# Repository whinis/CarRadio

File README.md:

# CarRadio
An atempt at making a fully featured car radio

There will be folders for each modules of the radio as well as one for the final board and all code needed to run the radio minus the si4689 firmware files

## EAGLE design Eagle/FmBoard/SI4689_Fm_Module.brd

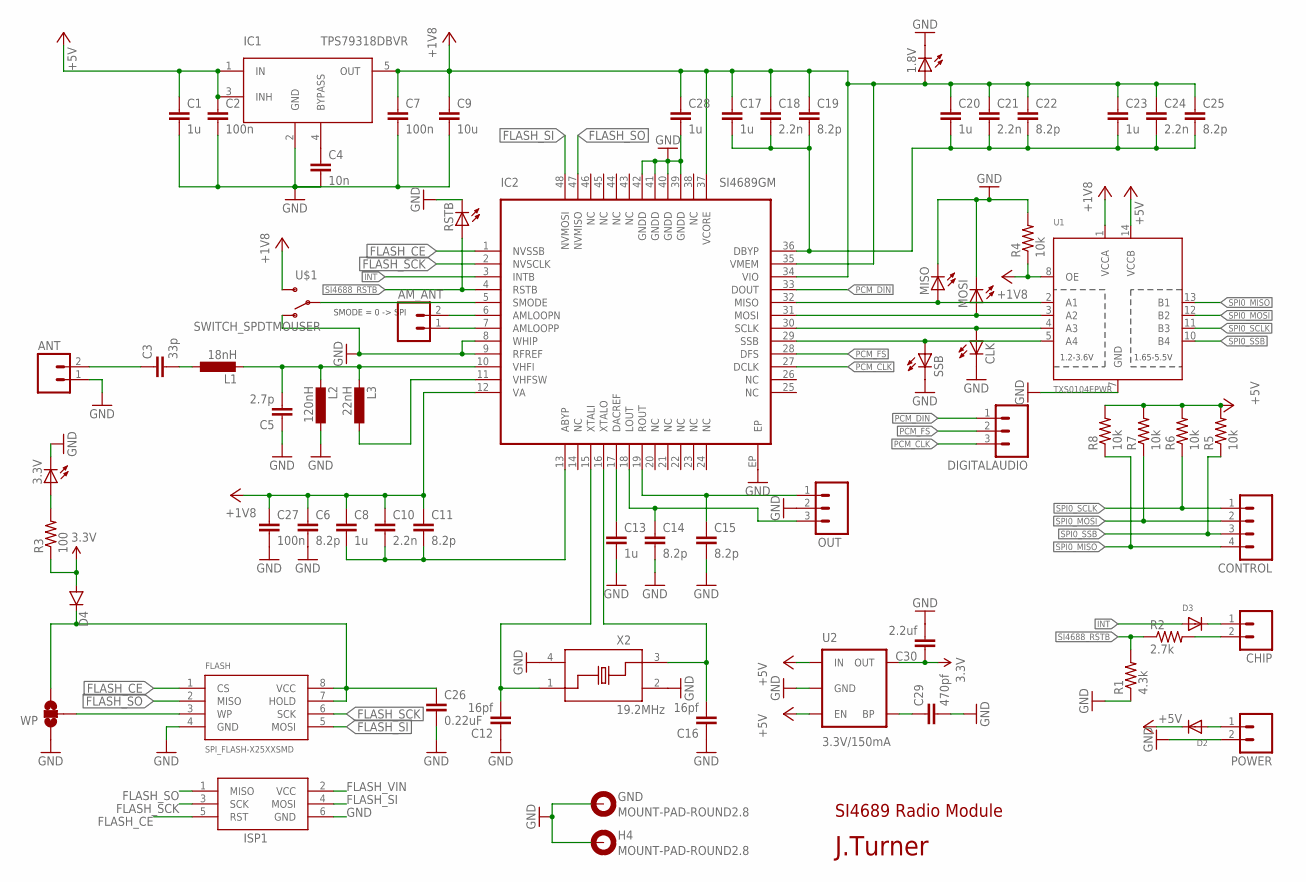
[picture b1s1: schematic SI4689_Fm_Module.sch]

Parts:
1.8V, 3.3V: LED_ESML0603; LED_SML0603
AM_ANT: M02; 02P
ANT: M02; 02P
C1, C8, C13, C17, C20, C23, C28: 1u; SMD0603
C2, C7, C27: 100n; SMD0603
C3: 33p; 0603-CAP
C4: 10n; SMD0603
C5: 2.7p; 0603-CAP
C6, C11, C14, C15, C19, C22, C25: 8.2p; SMD0603
C9: 10u; SMD0603
C10, C18, C21, C24: 2.2n; SMD0603
C12, C16: 16pf; 0603-CAP
C26: 0.22uF; 0603-CAP
C29: 470pf; 0603-CAP
C30: 2.2uf; 0603-CAP
CHIP: M02; 02P
CLK: LED_ESML0603; LED_SML0603
CONTROL: M04; 04P
D2, D3: DIODESOD-323F; SOD-323F
D4: DIODESOD523; SOD523
DIGITALAUDIO: M03; 03P
FLASH: SPI_FLASH-X25XXSMD; SO08
GND: MOUNT-PAD-ROUND2.8; 2,8-PAD
H4: MOUNT-PAD-ROUND2.8; 2,8-PAD
IC1: TPS79318DBVR; SOT23-5
IC2: SI4689GM; QFN48
ISP1: AVRISP-6; AVRISP
L1: 18nH; SMD0402
L2: 120nH; SMD0402
L3: 22nH; SMD0402
MISO: LED_ESML0603; LED_SML0603
MOSI: LED_ESML0603; LED_SML0603
OUT: M03; 03P
POWER: M02; 02P
R1: 4.3k; 0603-RES
R2: 2.7k; 0603-RES
R3: 100; 0603-RES
R4, R5, R6, R7, R8: 10k; 0603-RES
RSTB: LED_ESML0603; LED_SML0603
SSB: LED_ESML0603; LED_SML0603
U1: TXS0104EPWR; TSSOP14
U2: 3.3V/150mA; SOT23-5
U$1: SWITCH_SPDTMOUSER; SSSS810701
WP: SOLDERJUMPER_2WAYS; SJ_3
X2: 19.2MHz; XTAL_3.2X2.5

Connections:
3.3V: C30.1, D4.A, R3.1, U2.5 (OUT)
+1V8: 1.8V.A, C6.1, C7.1, C8.1, C9.1, C10.1, C11.1, C17.1, C18.1, C19.1, C20.1, C21.1, C22.1, C23.1, C24.1, C25.1, C27.1, C28.1, IC1.5 (OUT), IC2.12 (VA), IC2.34 (VIO), IC2.35 (VMEM), IC2.37 (VCORE), R4.1, U1.1 (VCCA), U1.8 (OE), U$1.S
FLASH_CE: FLASH.1 (CS), IC2.1 (NVSSB), ISP1.5 (RST)
FLASH_SCK: FLASH.6 (SCK), IC2.2 (NVSCLK), ISP1.3 (SCK)
FLASH_SI: FLASH.5 (MOSI), IC2.48 (NVMOSI), ISP1.4 (MOSI)
FLASH_SO: FLASH.2 (MISO), IC2.47 (NVMISO), ISP1.1 (MISO)
FLASH_VIN: C26.1, D4.C, FLASH.7 (HOLD), FLASH.8 (VCC), ISP1.2 (VCC), WP.3
GND: 1.8V.C, 3.3V.C, ANT.1, C1.2, C2.2, C4.2, C5.1, C6.2, C7.2, C9.2, C12.1, C13.2, C14.2, C15.2, C16.1, C26.2, C27.2, C28.2, C29.2, C30.2, CLK.C, FLASH.4 (GND), GND.B2,8, H4.B2,8, IC1.2 (GND), IC2.8 (WHIP), IC2.9 (RFREF), IC2.39 (GNDD), IC2.40 (GNDD), IC2.41 (GNDD), IC2.42 (GNDD), IC2.EP, ISP1.6 (GND), L2.1, MISO.C, MOSI.C, OUT.2, POWER.2, R1.1, R4.2, RSTB.C, SSB.C, U1.7 (GND), U2.2 (GND), U$1.O, WP.1, X2.2 (GND), X2.4 (GND)
INT: D3.A, IC2.3 (INTB)
LDO_IN: C1.1, C2.1, D2.C, IC1.1 (IN), IC1.3 (INH), R5.2, R6.2, R7.2, R8.2, U1.14 (VCCB), U2.1 (IN), U2.3 (EN)
unnamed: C3.2, L1.1
unnamed: C5.2, IC2.10 (VHFI), L1.2, L2.2, L3.2
unnamed: IC2.11 (VHFSW), L3.1
unnamed: C8.2, C10.2, C11.2, IC2.13 (ABYP)
unnamed: C17.2, C18.2, C19.2, C20.2, C21.2, C22.2, C23.2, C24.2, C25.2, IC2.36 (DBYP)
unnamed: C12.2, IC2.15 (XTALI), X2.1
unnamed: C16.2, IC2.16 (XTALO), X2.3
unnamed: C13.1, IC2.17 (DACREF)
unnamed: CHIP.1, D3.C
unnamed: C4.1, IC1.4 (BYPASS)
unnamed: C29.1, U2.4 (BP)
unnamed: 3.3V.A, R3.2
unnamed: FLASH.3 (WP), WP.2
unnamed: AM_ANT.1, IC2.7 (AMLOOPP)
unnamed: AM_ANT.2, IC2.6 (AMLOOPN)
unnamed: IC2.5 (SMODE), U$1.P
unnamed: CHIP.2, R2.2
unnamed: D2.A, POWER.1
PCM_CLK: DIGITALAUDIO.3, IC2.27 (DCLK)
PCM_DIN: DIGITALAUDIO.1, IC2.33 (DOUT)
PCM_FS: DIGITALAUDIO.2, IC2.28 (DFS)
RF_IN: ANT.2, C3.1
SI4688_LOUT: C14.1, IC2.18 (LOUT), OUT.3
SI4688_ROUT: C15.1, IC2.19 (ROUT), OUT.1
SI4688_RSTB: IC2.4 (RSTB), R1.2, R2.1, RSTB.A
SPI0_CE0_N18: IC2.29 (SSB), SSB.A, U1.5 (A4)
SPI0_MISO: CONTROL.4, R8.1, U1.13 (B1)
SPI0_MISO18: IC2.32 (MISO), MISO.A, U1.2 (A1)
SPI0_MOSI: CONTROL.2, R7.1, U1.12 (B2)
SPI0_MOSI18: IC2.31 (MOSI), MOSI.A, U1.3 (A2)
SPI0_SCLK: CONTROL.1, R6.1, U1.11 (B3)
SPI0_SCLK18: CLK.A, IC2.30 (SCLK), U1.4 (A3)
SPI0_SSB: CONTROL.3, R5.1, U1.10 (B4)

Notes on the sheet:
SI4689 Radio Module
SMODE = 0 -> SPI
J.Turner

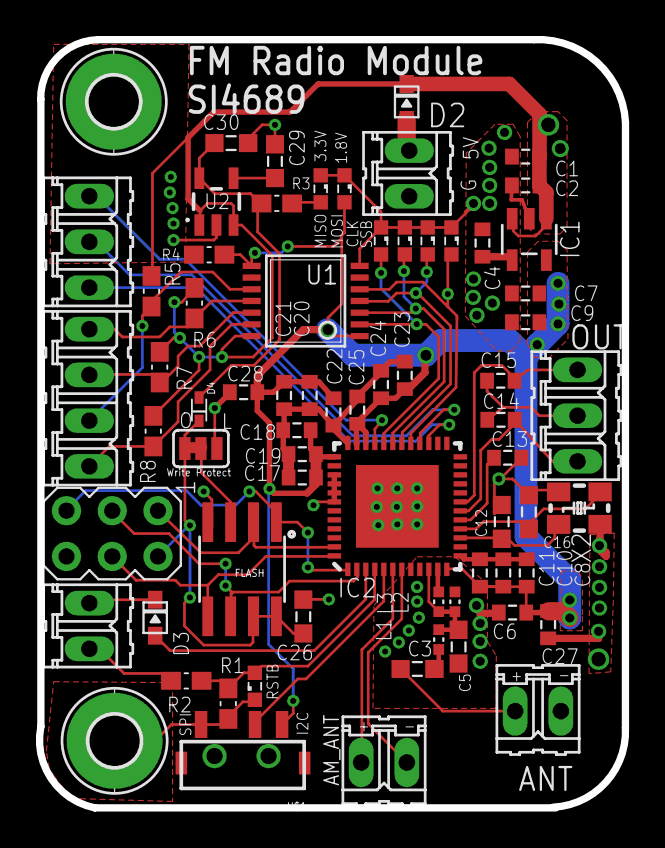
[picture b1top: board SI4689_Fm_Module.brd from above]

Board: 2 copper layers, 32.5 x 42.7 mm, 69 parts (0 on the bottom side), 43 nets.

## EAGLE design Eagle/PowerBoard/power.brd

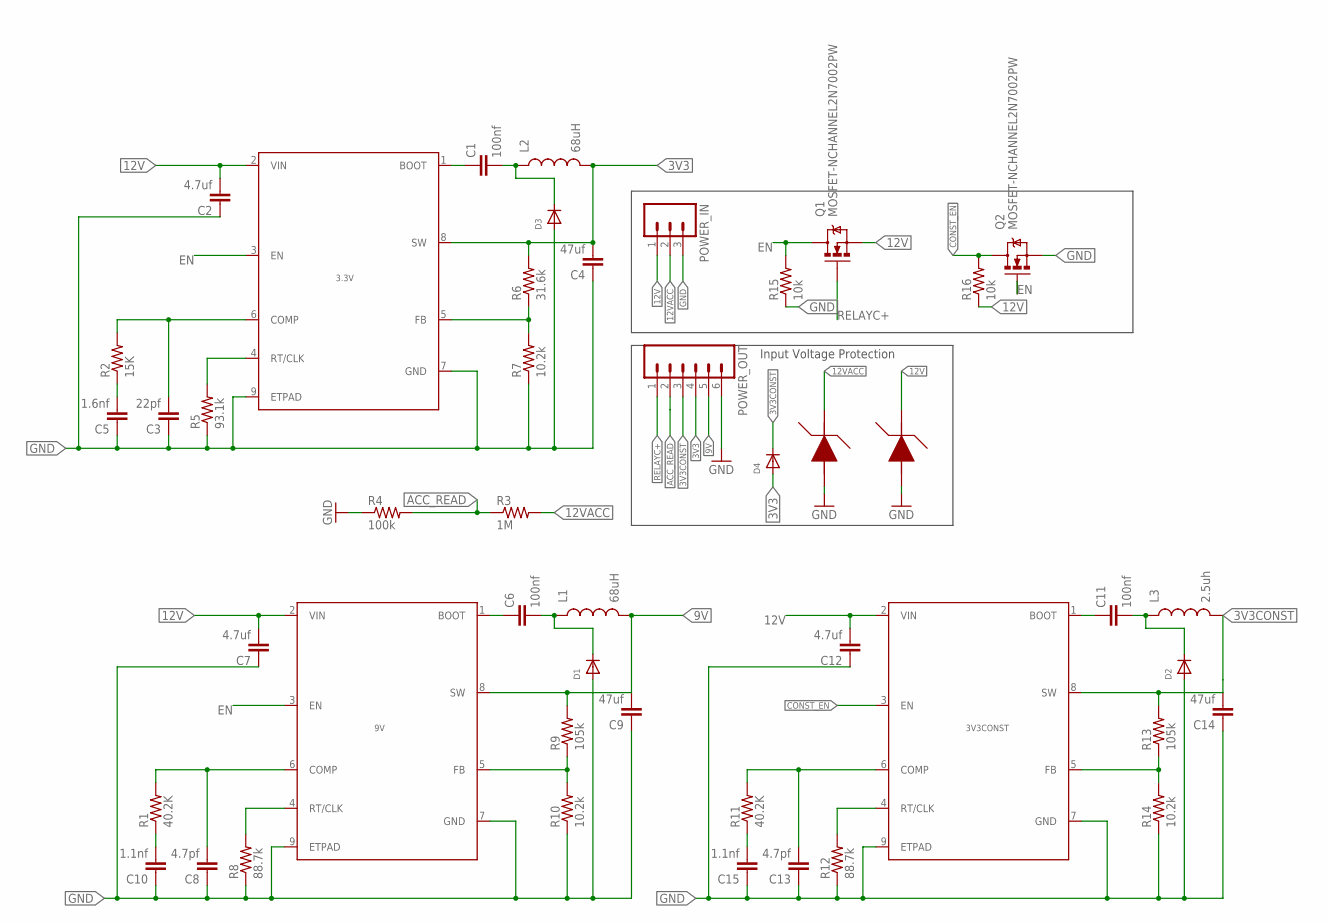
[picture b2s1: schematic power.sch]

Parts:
3.3V, 3V3CONST, 9V: TPS54340POWERPAD; DDA(R-PDSO-G08)
C1, C6, C11: 100nf; 0603-CAP
C2, C7, C12: 4.7uf; 0603-CAP
C3: 22pf; 0603-CAP
C4, C9, C14: 47uf; 0603-CAP
C5: 1.6nf; 0603-CAP
C8, C13: 4.7pf; 0603-CAP
C10, C15: 1.1nf; 0603-CAP
D1, D2, D3: DIODESOD-323F; SOD-323F
D4: DIODESOD-523; SOD-523
L1, L2: 68uH; CR75
L3: 2.5uh; CR54
POWER_IN: M03; 03P
POWER_OUT: M06; 06P
Q1, Q2: MOSFET-NCHANNEL2N7002PW; SOT323
R1, R11: 40.2K; 0603-RES
R2: 15K; 0603-RES
R3: 1M; 0603-RES
R4: 100k; 0603-RES
R5: 93.1k; 0603-RES
R6: 31.6k; 0603-RES
R7, R10, R14: 10.2k; 0603-RES
R8, R12: 88.7k; 0603-RES
R9, R13: 105k; 0603-RES
R15, R16: 10k; 0603-RES
U$3, U$5: SMCJ12A; DO-214AC

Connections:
3V3: 3.3V.8 (SW), C4.2, D4.A, L2.P$2 (2), POWER_OUT.4, R6.2
3V3CONST: 3V3CONST.8 (SW), C14.2, D4.K (C), L3.P$2 (2), POWER_OUT.3, R13.2
9V: 9V.8 (SW), C9.2, L1.P$2 (2), POWER_OUT.5, R9.2
12V: 3.3V.2 (VIN), 3V3CONST.2 (VIN), 9V.2 (VIN), C2.2, C7.2, C12.2, POWER_IN.1, Q1.2 (S), R16.1, U$5.NEG (GND)
12VACC: POWER_IN.2, R3.2, U$3.NEG (GND)
ACC_READ: POWER_OUT.2, R3.1, R4.2
CONST_EN: 3V3CONST.3 (EN), Q2.3 (D), R16.2
EN: 3.3V.3 (EN), 9V.3 (EN), Q1.3 (D), Q2.1 (G), R15.2
GND: 3.3V.7 (GND), 3.3V.9 (ETPAD), 3V3CONST.7 (GND), 3V3CONST.9 (ETPAD), 9V.7 (GND), 9V.9 (ETPAD), C2.1, C3.1, C4.1, C5.1, C7.1, C8.1, C9.1, C10.1, C12.1, C13.1, C14.1, C15.1, D1.A, D2.A, D3.A, POWER_IN.3, POWER_OUT.6, Q2.2 (S), R4.1, R5.1, R7.1, R8.1, R10.1, R12.1, R14.1, R15.1, U$3.POS (VIN), U$5.POS (VIN)
unnamed: C10.2, R1.1
unnamed: C5.2, R2.1
unnamed: 3.3V.6 (COMP), C3.2, R2.2
unnamed: 3.3V.4 (RT/CLK), R5.2
unnamed: C1.2, D3.C, L2.P$1 (1)
unnamed: 3.3V.5 (FB), R6.1, R7.2
unnamed: 9V.6 (COMP), C8.2, R1.2
unnamed: 3.3V.1 (BOOT), C1.1
unnamed: 9V.4 (RT/CLK), R8.2
unnamed: 9V.5 (FB), R9.1, R10.2
unnamed: 9V.1 (BOOT), C6.1
unnamed: C6.2, D1.C, L1.P$1 (1)
unnamed: C15.2, R11.1
unnamed: 3V3CONST.6 (COMP), C13.2, R11.2
unnamed: 3V3CONST.4 (RT/CLK), R12.2
unnamed: 3V3CONST.5 (FB), R13.1, R14.2
unnamed: 3V3CONST.1 (BOOT), C11.1
unnamed: C11.2, D2.C, L3.P$1 (1)
RELAYC+: POWER_OUT.1, Q1.1 (G)

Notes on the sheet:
Input Voltage Protection

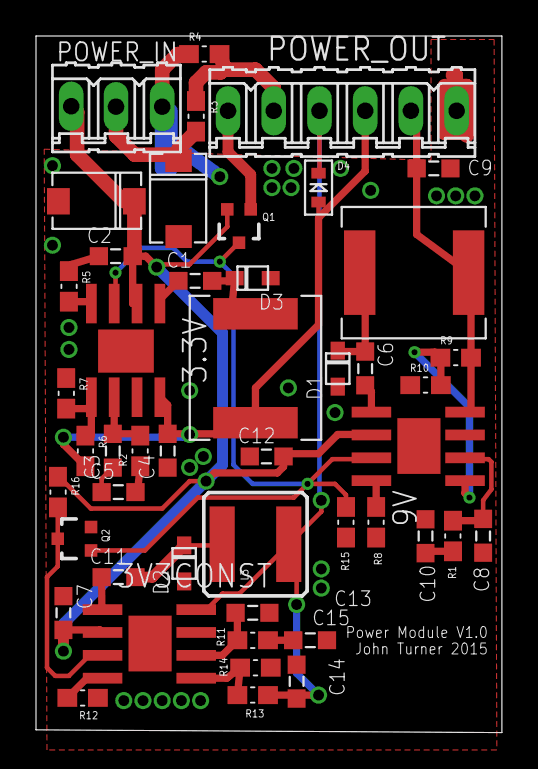
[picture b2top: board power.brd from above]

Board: 2 copper layers, 25.9 x 38.7 mm, 47 parts (0 on the bottom side), 28 nets.

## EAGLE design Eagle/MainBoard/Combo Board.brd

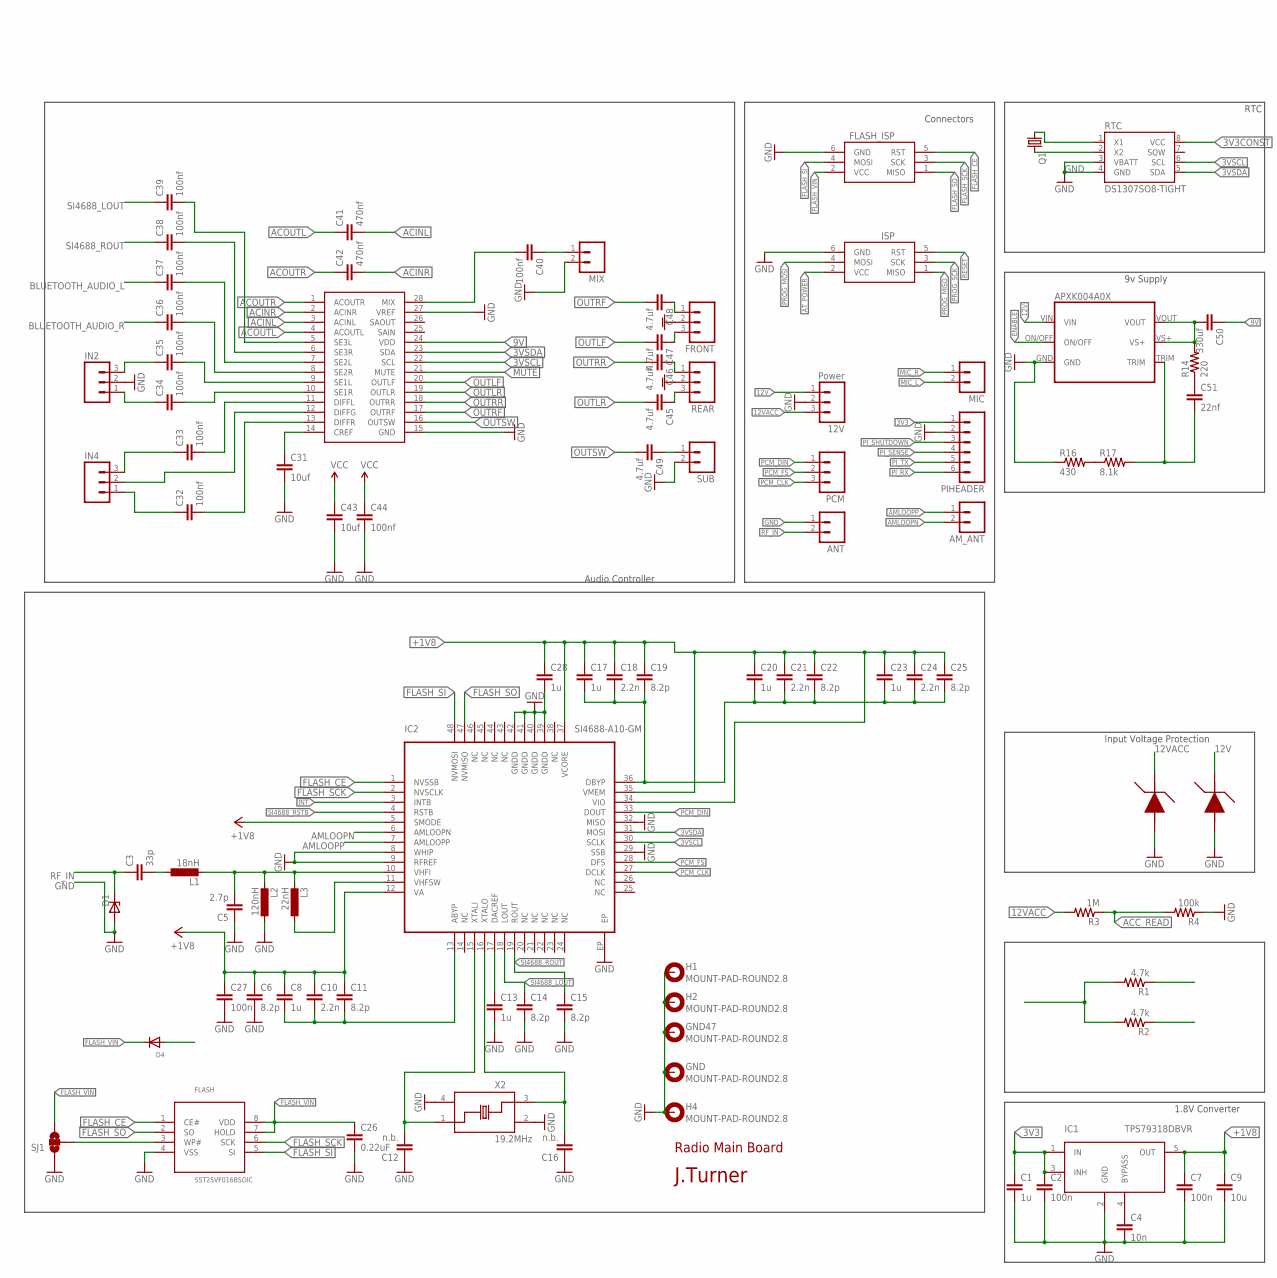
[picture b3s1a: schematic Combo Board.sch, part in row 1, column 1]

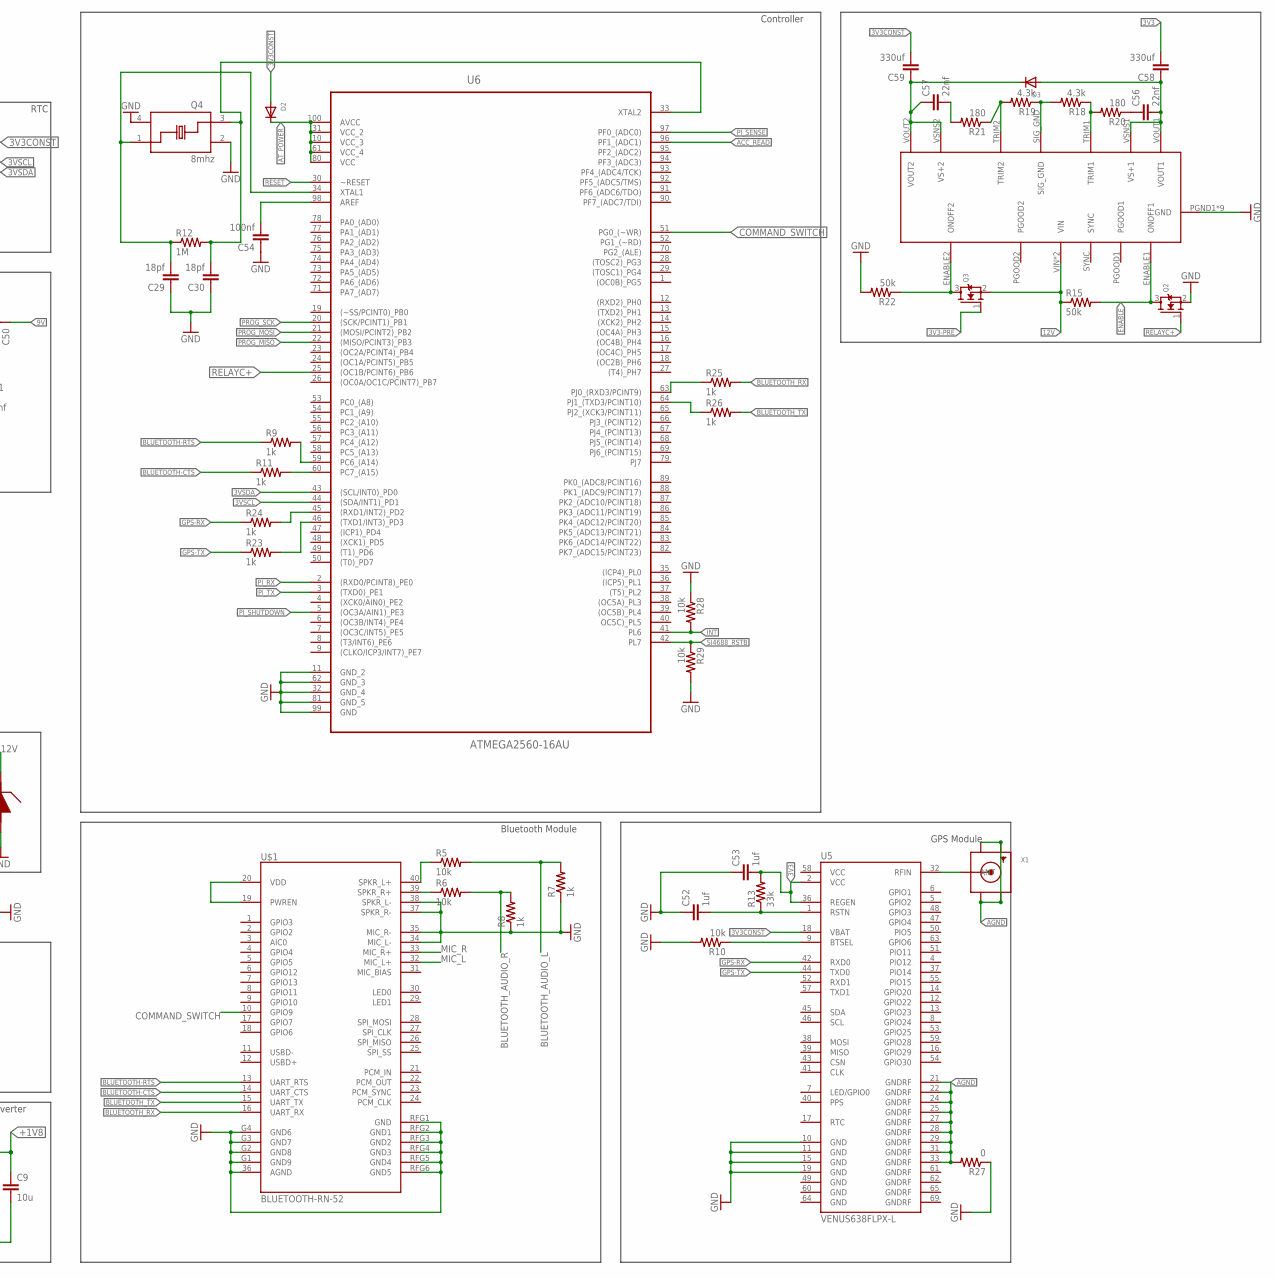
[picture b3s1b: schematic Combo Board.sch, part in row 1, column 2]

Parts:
12V: Power; 03P
AM_ANT: M02; 02P
ANT: M02; 02P
APXK004A0X: APXW005A0X3-SRZ; APXW005A0X3
C1, C8, C13, C17, C20, C23, C28: 1u; SMD0603
C2, C7, C27: 100n; SMD0603
C3: 33p; 0603-CAP
C4: 10n; SMD0603
C5: 2.7p; 0603-CAP
C6, C11, C14, C15, C19, C22, C25: 8.2p; SMD0603
C9: 10u; SMD0603
C10, C18, C21, C24: 2.2n; SMD0603
C12, C16: n.b.; 0603-CAP
C26: 0.22uF; 0603-CAP
C29, C30: 18pf; 0603-CAP
C31, C43: 10uf; 0603-CAP
C32, C33, C34, C35, C36, C37, C38, C39, C40, C44, C54: 100nf; 0603-CAP
C41, C42: 470nf; 0603-CAP
C45, C46, C47, C48, C49: 4.7uf; 0603-CAP
C50, C58, C59: 330uf; 0603-CAP
C51, C56, C57: 22nf; 0603-CAP
C52, C53: 1uf; SMD0603
D1: ESD9L5.0; SOD923
D2: DIODESOD-123; SOD-123
D3, D4: DIODESOD-323F; SOD-323F
FLASH: SST25VF016BSOIC; SOIC8
FLASH_ISP: AVRISP-6; AVRISP
FRONT: M03PTH; 1X03
GND, GND47: MOUNT-PAD-ROUND2.8; 2,8-PAD
H1, H2, H4: MOUNT-PAD-ROUND2.8; 2,8-PAD
IC1: TPS79318DBVR; SOT23-5
IC2: SI4688-A10-GM; QFN48
IN2, IN4: M03; 03P
ISP: AVRISP-6; AVRISP
L1: 18nH; SMD0402
L2: 120nH; SMD0402
L3: 22nH; SMD0402
MIC: M02; 02P
MIX: M02; 02P
PCM: M03; 03P
PIHEADER: M06; 06P
Q1: CRYSTALTC26H_EZ; TC26HEZ
Q2, Q3: MOSFET-NREFLOW; SOT23
Q4: 8mhz; XTAL_3.2X2.5
R1, R2: 4.7k; 0603-RES
R3, R12: 1M; 0603-RES
R4: 100k; 0603-RES
R5, R6, R10, R28, R29: 10k; 0603-RES
R7, R8, R9, R11, R23, R24, R25, R26: 1k; 0603-RES
R13: 33k; 0603-RES
R14: 220; 0603-RES
R15, R22: 50k; 0603-RES
R16: 430; 0603-RES
R17: 8.1k; 0603-RES
R18, R19: 4.3k; 0603-RES
R20, R21: 180; 0603-RES
R27: 0; 0603-RES
REAR: M03PTH; 1X03
RTC: DS1307SO8-TIGHT; SO08-TIGHT
SJ1: SOLDERJUMPER_2WAYS; SJ_3
SUB: M02; 02P
TDA: TDA7419; SOIC-28
U5: VENUS638FLPX-L; VENUS638FLPX
U6: ATMEGA2560-16AU; QFP50P1600X1600X120-100N
U$1: BLUETOOTH-RN-52; RN-52
U$2, U$3: SMCJ12A; DO-214AC
U$4: UVXS0606A0X3-SRZ; UVXS0606
X1: SMACONNECTOR; SMA90_DIP
X2: 19.2MHz; XTAL_3.2X2.5

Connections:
3V3: C1.1, C2.1, C53.2, C58.2, D4.A, IC1.1 (IN), IC1.3 (INH), PIHEADER.1, R1.2, R2.2, R13.2, U5.2 (VCC), U5.36 (REGEN), U$1.19 (PWREN), U$1.20 (VDD)
3V3-PRE: C56.2, C58.1, D3.A, Q3.1 (G), U$4.VOUT1, U$4.VSNS1 (VS+1)
3V3CONST: C59.2, D2.A, RTC.8 (VCC), U5.18 (VBAT)
3VSCL: IC2.30 (SCLK), R1.1, RTC.6 (SCL), TDA.22 (SCL), U6.44 ((SDA/INT1)_PD1)
3VSDA: IC2.31 (MOSI), R2.1, RTC.5 (SDA), TDA.23 (SDA), U6.43 ((SCL/INT0)_PD0)
9V: C43.1, C44.1, C50.1, TDA.24 (VDD)
12V: 12V.1, APXK004A0X.VIN, Q3.2 (S), R15.1, U$3.NEG (GND), U$4.VIN, U$4.VIN2 (VIN)
12VACC: 12V.3, R3.2, U$2.NEG (GND)
+1V8: C6.1, C7.1, C8.1, C9.1, C10.1, C11.1, C17.1, C18.1, C19.1, C20.1, C21.1, C22.1, C23.1, C24.1, C25.1, C27.1, C28.1, IC1.5 (OUT), IC2.5 (SMODE), IC2.12 (VA), IC2.34 (VIO), IC2.35 (VMEM), IC2.37 (VCORE)
ACC_READ: R3.1, R4.2, U6.96 (PF1_(ADC1))
ACINL: C41.2, TDA.3 (ACINL)
ACINR: C42.2, TDA.2 (ACINR)
ACOUTL: C41.1, TDA.4 (ACOUTL)
ACOUTR: C42.1, TDA.1 (ACOUTR)
AGND: R27.2, U5.21 (GNDRF), U5.22 (GNDRF), U5.24 (GNDRF), U5.25 (GNDRF), U5.27 (GNDRF), U5.28 (GNDRF), U5.29 (GNDRF), U5.31 (GNDRF), U5.33 (GNDRF), X1.GND1, X1.GND2, X1.GND3, X1.GND4
AMLOOPN: AM_ANT.2, IC2.6 (AMLOOPN)
AMLOOPP: AM_ANT.1, IC2.7 (AMLOOPP)
AT_POWER: D2.C, ISP.2 (VCC), U6.10 (VCC_3), U6.31 (VCC_2), U6.61 (VCC_4), U6.80 (VCC), U6.100 (AVCC)
BLUETOOTH-CTS: R11.1, U$1.14 (UART_CTS)
BLUETOOTH-RTS: R9.1, U$1.13 (UART_RTS)
BLUETOOTH_AUDIO_L: C37.1, R5.2, R7.2
BLUETOOTH_AUDIO_R: C36.1, R6.2, R8.2
BLUETOOTH_RX: R25.2, U$1.16 (UART_RX)
BLUETOOTH_TX: R26.2, U$1.15 (UART_TX)
COMMAND_SWITCH: U6.51 (PG0_(~WR)), U$1.10 (GPIO9)
CREF: C31.1, TDA.14 (CREF)
DIFFG: IN4.2, TDA.12 (DIFFG)
DIFFL: C33.2, TDA.11 (DIFFL)
DIFFR: C32.2, TDA.13 (DIFFR)
ENABLE: APXK004A0X.ON/OFF, Q2.3 (D), R15.2, U$4.ENABLE1 (ONOFF1)
FLASH_CE: FLASH.1 (CE#), FLASH_ISP.5 (RST), IC2.1 (NVSSB)
FLASH_SCK: FLASH.6 (SCK), FLASH_ISP.3 (SCK), IC2.2 (NVSCLK)
FLASH_SI: FLASH.5 (SI), FLASH_ISP.4 (MOSI), IC2.48 (NVMOSI)
FLASH_SO: FLASH.2 (SO), FLASH_ISP.1 (MISO), IC2.47 (NVMISO)
FLASH_VIN: C26.1, D4.C, FLASH.7 (HOLD), FLASH.8 (VDD), FLASH_ISP.2 (VCC), SJ1.3
GND: 12V.2, ANT.1, APXK004A0X.GND, C1.2, C2.2, C4.2, C5.1, C6.2, C7.2, C9.2, C12.1, C13.2, C14.2, C15.2, C16.1, C26.2, C27.2, C28.2, C29.1, C30.1, C31.2, C43.2, C44.2, C52.1, C53.1, C54.1, D1.A, FLASH.4 (VSS), FLASH_ISP.6 (GND), FRONT.2, GND.B2,8, GND47.B2,8, H1.B2,8, H2.B2,8, H4.B2,8, IC1.2 (GND), IC2.8 (WHIP), IC2.9 (RFREF), IC2.29 (SSB), IC2.32 (MISO), IC2.39 (GNDD), IC2.40 (GNDD), IC2.41 (GNDD), IC2.42 (GNDD), IC2.EP, IN2.2, ISP.6 (GND), L2.1, MIX.2, PIHEADER.2, Q2.2 (S), Q4.2 (GND), Q4.4 (GND), R4.1, R7.1, R8.1, R10.2, R16.1, R22.2, R27.1, R28.1, R29.2, REAR.2, RTC.3 (VBATT), RTC.4 (GND), SJ1.1, SUB.2, TDA.15 (GND), TDA.27 (VREF), U5.10 (GND), U5.11 (GND), U5.15 (GND), U5.19 (GND), U6.11 (GND_2), U6.32 (GND_4), U6.62 (GND_3), U6.81 (GND_5), U6.99 (GND), U$1.34 (MIC_L-), U$1.35 (MIC_R-), U$1.36 (AGND), U$1.37 (SPKR_R-), U$1.38 (SPKR_L-), U$1.G1 (GND9), U$1.G2 (GND8), U$1.G3 (GND7), U$1.G4 (GND6), U$1.RFG1 (GND), U$1.RFG2 (GND1), U$1.RFG3 (GND2), U$1.RFG4 (GND3), U$1.RFG5 (GND4), U$1.RFG6 (GND5), U$2.POS (VIN), U$3.POS (VIN), U$4.PGND1 (GND), U$4.PGND2 (GND), U$4.PGND3 (GND), U$4.PGND4 (GND), U$4.PGND5 (GND), U$4.PGND6 (GND), U$4.PGND7 (GND), U$4.PGND8 (GND), U$4.PGND9 (GND), X2.2 (GND), X2.4 (GND)
GPS-RX: R24.1, U5.42 (RXD0)
GPS-TX: R23.1, U5.44 (TXD0)
INT: IC2.3 (INTB), R28.2, U6.41 (PL6)
MIC_L: MIC.2, U$1.32 (MIC_L+)
MIC_R: MIC.1, U$1.33 (MIC_R+)
MIX: C40.2, TDA.28 (MIX)
MUTE: TDA.21 (MUTE)
unnamed: C3.2, L1.1
unnamed: C5.2, IC2.10 (VHFI), L1.2, L2.2, L3.2
unnamed: IC2.11 (VHFSW), L3.1
unnamed: C8.2, C10.2, C11.2, IC2.13 (ABYP)
unnamed: C17.2, C18.2, C19.2, C20.2, C21.2, C22.2, C23.2, C24.2, C25.2, IC2.36 (DBYP)
unnamed: C12.2, IC2.15 (XTALI), X2.1
unnamed: C16.2, IC2.16 (XTALO), X2.3
unnamed: C13.1, IC2.17 (DACREF)
unnamed: R9.2, U6.59 (PC6_(A14))
unnamed: C4.1, IC1.4 (BYPASS)
unnamed: R11.2, U6.60 (PC7_(A15))
unnamed: C30.2, Q4.3, R12.2, U6.33 (XTAL2)
unnamed: FLASH.3 (WP#), SJ1.2
unnamed: R5.1, U$1.40 (SPKR_L+)
unnamed: R6.1, U$1.39 (SPKR_R+)
unnamed: APXK004A0X.TRIM, C51.2, R17.2
unnamed: C40.1, MIX.1
unnamed: Q1.2, RTC.2 (X2)
unnamed: Q1.1, RTC.1 (X1)
unnamed: C35.1, IN2.3
unnamed: C34.1, IN2.1
unnamed: R23.2, U6.46 ((TXD1/INT3)_PD3)
unnamed: C29.2, Q4.1, R12.1, U6.34 (XTAL1)
unnamed: C33.1, IN4.3
unnamed: C32.1, IN4.1
unnamed: R24.2, U6.45 ((RXD1/INT2)_PD2)
unnamed: R16.2, R17.1
unnamed: R10.1, U5.9 (BTSEL)
unnamed: C52.2, R13.1, U5.1 (RSTN)
unnamed: C48.1, FRONT.1
unnamed: C47.1, FRONT.3
unnamed: C46.1, REAR.1
unnamed: C45.1, REAR.3
unnamed: C49.1, SUB.1
unnamed: APXK004A0X.VOUT, APXK004A0X.VS+, C50.2, R14.2
unnamed: C51.1, R14.1
unnamed: R19.2, R21.1, U$4.TRIM2
unnamed: R18.1, R20.2, U$4.TRIM1
unnamed: C56.1, R20.1
unnamed: C57.2, R21.2
unnamed: R18.2, R19.1, U$4.SIG_GND
unnamed: C57.1, C59.1, D3.C, U$4.VOUT2, U$4.VSNS2 (VS+2)
unnamed: R25.1, U6.63 (PJ0_(RXD3/PCINT9))
unnamed: R26.1, U6.64 (PJ1_(TXD3/PCINT10))
unnamed: Q3.3 (D), R22.1, U$4.ENABLE2 (ONOFF2)
unnamed: C54.2, U6.98 (AREF)
unnamed: U5.32 (RFIN), X1.ANTENNA (ANT)
OUTLF: C47.2, TDA.20 (OUTLF)
OUTLR: C45.2, TDA.19 (OUTLR)
OUTRF: C48.2, TDA.17 (OUTRF)
OUTRR: C46.2, TDA.18 (OUTRR)
OUTSW: C49.2, TDA.16 (OUTSW)
PCM_CLK: IC2.27 (DCLK), PCM.3
PCM_DIN: IC2.33 (DOUT), PCM.1
PCM_FS: IC2.28 (DFS), PCM.2
PI_RX: PIHEADER.6, U6.2 ((RXD0/PCINT8)_PE0)
PI_SENSE: PIHEADER.4, U6.97 (PF0_(ADC0))
PI_SHUTDOWN: PIHEADER.3, U6.5 ((OC3A/AIN1)_PE3)
PI_TX: PIHEADER.5, U6.3 ((TXD0)_PE1)
PROG_MISO: ISP.1 (MISO), U6.22 ((MISO/PCINT3)_PB3)
PROG_MOSI: ISP.4 (MOSI), U6.21 ((MOSI/PCINT2)_PB2)
PROG_SCK: ISP.3 (SCK), U6.20 ((SCK/PCINT1)_PB1)
RELAYC+: Q2.1 (G), U6.25 ((OC1B/PCINT6)_PB6)
RESET: ISP.5 (RST), U6.30 (~RESET)
RF_IN: ANT.2, C3.1, D1.K (C)
SE1L: C35.2, TDA.9 (SE1L)
SE1R: C34.2, TDA.10 (SE1R)
SE2L: C37.2, TDA.7 (SE2L)
SE2R: C36.2, TDA.8 (SE2R)
SE3L: C39.2, TDA.5 (SE3L)
SE3R: C38.2, TDA.6 (SE3R)
SI4688_LOUT: C14.1, C39.1, IC2.18 (LOUT)
SI4688_ROUT: C15.1, C38.1, IC2.19 (ROUT)
SI4688_RSTB: IC2.4 (RSTB), R29.1, U6.42 (PL7)

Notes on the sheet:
Radio Main Board
J.Turner
RTC
Audio Controller
1.8V Converter
Input Voltage Protection
9v Supply
Connectors
Controller
GPS Module
Bluetooth Module

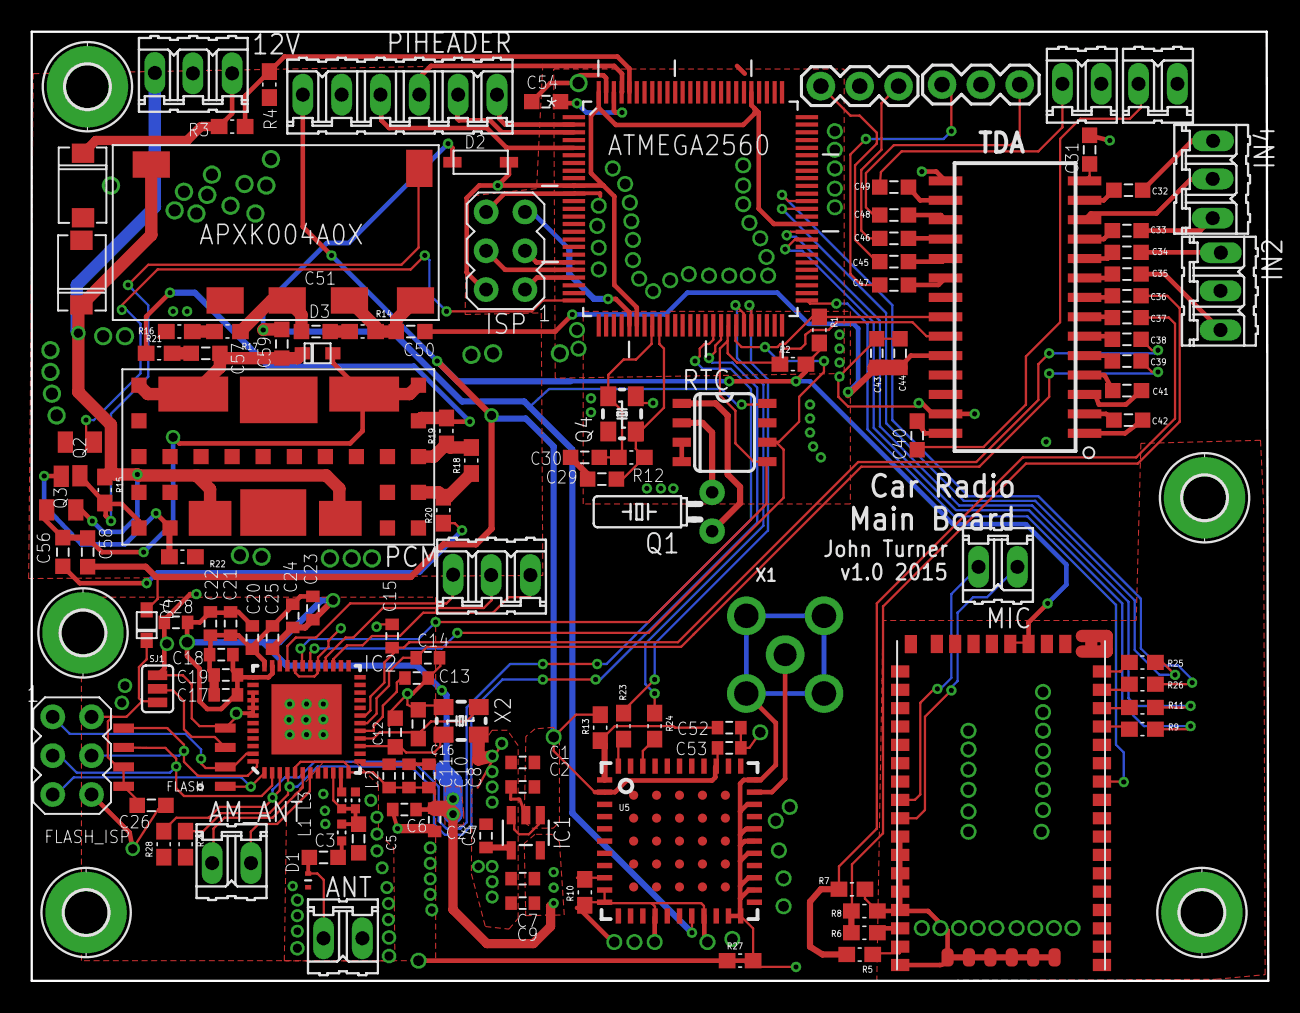
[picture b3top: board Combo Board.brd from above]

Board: 2 copper layers, 80.9 x 62.1 mm, 132 parts (0 on the bottom side), 116 nets.

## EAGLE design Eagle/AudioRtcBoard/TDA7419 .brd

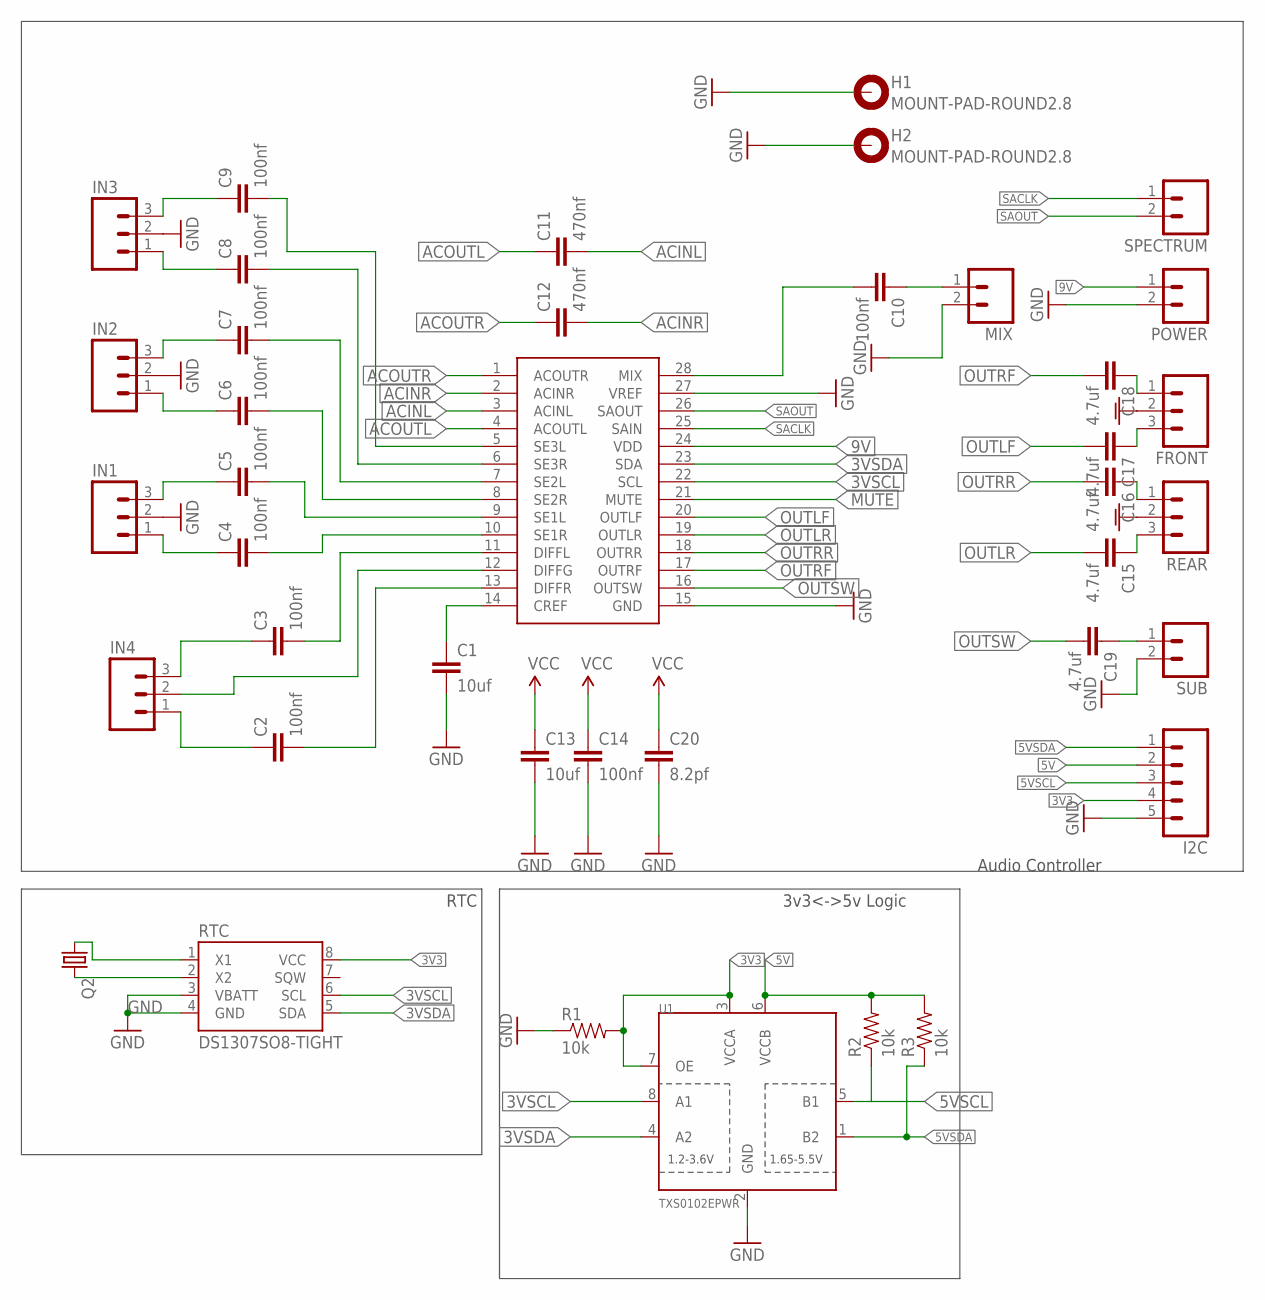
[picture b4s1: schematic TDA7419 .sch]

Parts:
C1, C13: 10uf; 0603-CAP
C2, C3, C4, C5, C6, C7, C8, C9, C10, C14: 100nf; 0603-CAP
C11, C12: 470nf; 0603-CAP
C15, C16, C17, C18, C19: 4.7uf; 0603-CAP
C20: 8.2pf; 0603-CAP
FRONT: M03PTH; 1X03
H1, H2: MOUNT-PAD-ROUND2.8; 2,8-PAD
I2C: M05; 05P
IN1, IN2, IN3, IN4: M03; 03P
MIX: M02; 02P
POWER: M02; 02P
Q2: CRYSTALTC26H_EZ; TC26HEZ
R1, R2, R3: 10k; 0603-RES
REAR: M03PTH; 1X03
RTC: DS1307SO8-TIGHT; SO08-TIGHT
SPECTRUM: M02; 02P
SUB: M02; 02P
TDA: TDA7419; SOIC-28
U1: TXS0102EPWR; TSSOP8

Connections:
3V3: I2C.4, R1.2, RTC.8 (VCC), U1.3 (VCCA), U1.7 (OE)
3VSCL: RTC.6 (SCL), TDA.22 (SCL), U1.8 (A1)
3VSDA: RTC.5 (SDA), TDA.23 (SDA), U1.4 (A2)
5V: I2C.2, R2.2, R3.2, U1.6 (VCCB)
5VSCL: I2C.3, R2.1, U1.5 (B1)
5VSDA: I2C.1, R3.1, U1.1 (B2)
9V: C13.1, C14.1, C20.1, POWER.1, TDA.24 (VDD)
ACINL: C11.2, TDA.3 (ACINL)
ACINR: C12.2, TDA.2 (ACINR)
ACOUTL: C11.1, TDA.4 (ACOUTL)
ACOUTR: C12.1, TDA.1 (ACOUTR)
CREF: C1.1, TDA.14 (CREF)
DIFFG: IN4.2, TDA.12 (DIFFG)
DIFFL: C3.2, TDA.11 (DIFFL)
DIFFR: C2.2, TDA.13 (DIFFR)
GND: C1.2, C13.2, C14.2, C20.2, FRONT.2, H1.B2,8, H2.B2,8, I2C.5, IN1.2, IN2.2, IN3.2, MIX.2, POWER.2, R1.1, REAR.2, RTC.3 (VBATT), RTC.4 (GND), SUB.2, TDA.15 (GND), TDA.27 (VREF), U1.2 (GND)
MIX: C10.2, TDA.28 (MIX)
MUTE: TDA.21 (MUTE)
unnamed: C10.1, MIX.1
unnamed: C9.1, IN3.3
unnamed: C8.1, IN3.1
unnamed: C7.1, IN2.3
unnamed: C6.1, IN2.1
unnamed: C5.1, IN1.3
unnamed: C4.1, IN1.1
unnamed: C3.1, IN4.3
unnamed: C2.1, IN4.1
unnamed: C18.1, FRONT.1
unnamed: C17.1, FRONT.3
unnamed: C16.1, REAR.1
unnamed: C15.1, REAR.3
unnamed: C19.1, SUB.1
unnamed: Q2.2, RTC.2 (X2)
unnamed: Q2.1, RTC.1 (X1)
OUTLF: C17.2, TDA.20 (OUTLF)
OUTLR: C15.2, TDA.19 (OUTLR)
OUTRF: C18.2, TDA.17 (OUTRF)
OUTRR: C16.2, TDA.18 (OUTRR)
OUTSW: C19.2, TDA.16 (OUTSW)
SACLK: SPECTRUM.1, TDA.25 (SAIN)
SAOUT: SPECTRUM.2, TDA.26 (SAOUT)
SE1L: C5.2, TDA.9 (SE1L)
SE1R: C4.2, TDA.10 (SE1R)
SE2L: C7.2, TDA.7 (SE2L)
SE2R: C6.2, TDA.8 (SE2R)
SE3L: C9.2, TDA.5 (SE3L)
SE3R: C8.2, TDA.6 (SE3R)

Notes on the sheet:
Audio Controller
RTC
3v3<->5v Logic

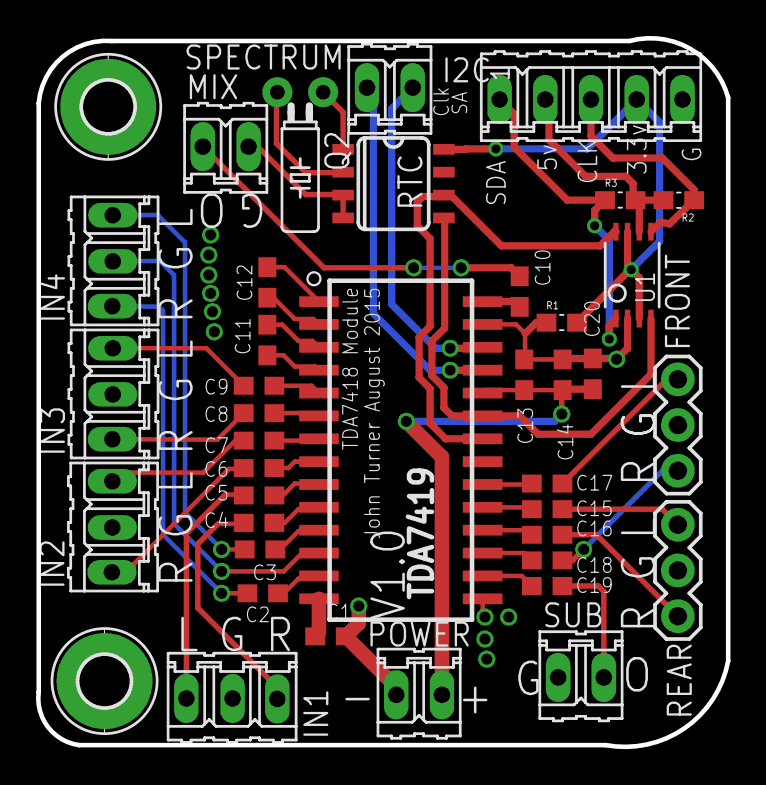
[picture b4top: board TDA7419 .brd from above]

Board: 2 copper layers, 38.3 x 39.4 mm, 40 parts (0 on the bottom side), 46 nets.

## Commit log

2016-03-05 Initial Commit of the private work I have done so far
2016-06-12 Small update and removing of the FirmwareLoader that doesn't work.
2016-11-11 Updated to the now working v1.7 of the radio module Made Radio Module arudino compatible so that it can be plugged directly into the arudino Moved to a S25FL132K0XMFI041 flash chip due to being cheap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
2016-11-11 Initial commit of my python application that communicates with the SI468x series radio chip Basic commands for now and communicates of a ft232h chip over usb Switched to python and ft232h instead of 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

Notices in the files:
parts and their libraries:
SparkFun-Connectors: Licensing: CC v3.0 Share-Alike You are welcome to use this library for commercial purposes.
SparkFun-FreqCtrl: Licensing: Creative Commons ShareAlike 4.0 International - https://creativecommons.org/licenses/by-sa/4.0
